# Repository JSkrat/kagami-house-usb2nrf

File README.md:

# Kagami house v3 — concentrator

usb to nrf24l01 radio network convertor

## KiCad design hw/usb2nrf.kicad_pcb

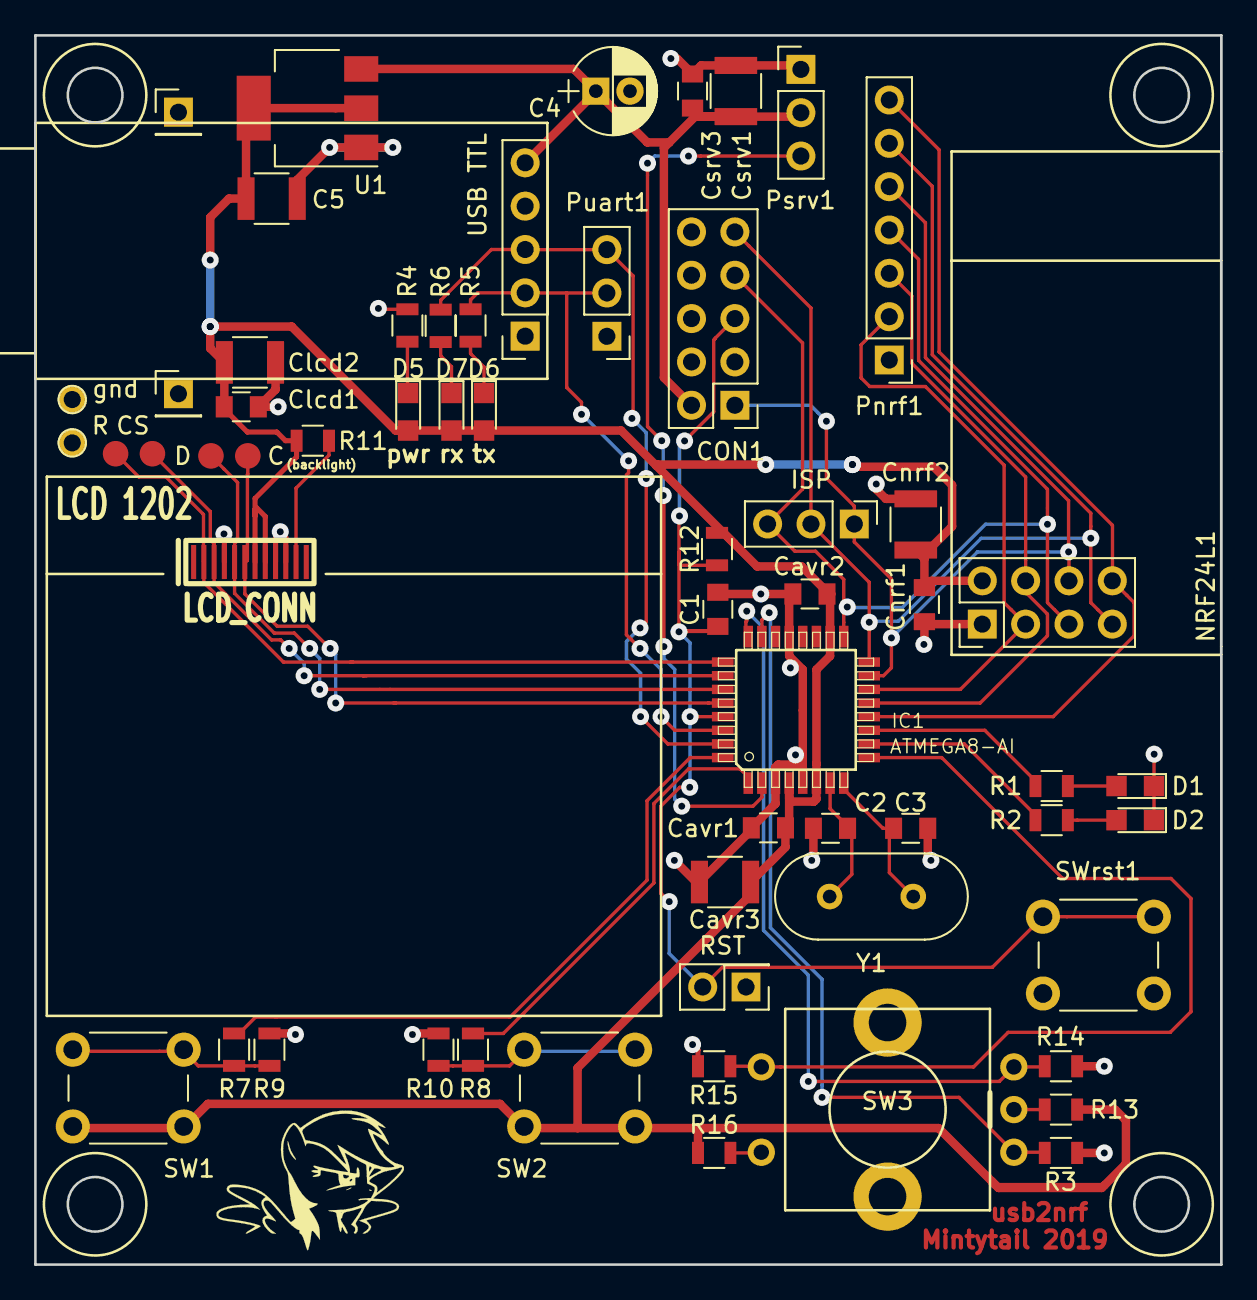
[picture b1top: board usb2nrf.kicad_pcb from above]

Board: 2 copper layers, 69.5 x 72.0 mm, 58 parts (0 on the bottom side), 36 nets.

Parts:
C: Measurement_Point_Round-SMD-Pad_Small
C1: 100n; C_0805
C2, C3: 22p; C_0805
C4: 10u; CP_Radial_D5.0mm_P2.00mm
C5: 10u; C_1210
CON1: AVR-JTAG-10; Pin_Header_Straight_2x05_Pitch2.54mm
CS: Measurement_Point_Round-SMD-Pad_Small
Cavr1, Cavr2: 100n; C_0805
Cavr3: 10u; C_1210
Clcd1: 100n; C_0805
Clcd2: 10u; C_1210
Cnrf1: 100n; C_0805
Cnrf2: 10u; C_1210
Csrv1: 10u; C_1210
Csrv3: 100n; C_0805
D: Measurement_Point_Round-SMD-Pad_Small
D1, D2, D5, D6, D7: LED; LED_0805
IC1: ATMEGA8-AI; atmega8-TQFP32-08
ISP: CONN_01X03; Pin_Header_Straight_1x03_Pitch2.54mm
LCD 1202: LCD_CONN; SIL-12
NRF24L1: NRF24L01; Pin_Header_Straight_2x04_Pitch2.54mm
P3, P6: CONN_01X01; Pin_Header_Straight_1x01_Pitch2.54mm
Pnrf1: nrf_test; Pin_Header_Straight_1x07_Pitch2.54mm
Psrv1: CONN_srv; Pin_Header_Straight_1x03_Pitch2.54mm
Puart1: uart_test; Pin_Header_Straight_1x03_Pitch2.54mm
R: Measurement_Point_Round-SMD-Pad_Small
R1, R2, R4, R5, R6, R11: R; R_0805
R3, R9, R10, R14, R15: 10k; R_0805
R7, R8: 150; R_0805
R12: 47k; R_0805
R13, R16: 511; R_0805
RST: CONN_01X02; Pin_Header_Straight_2x01_Pitch2.54mm
SW1, SW2: SW_Push; SW_PUSH_6mm_h4.3mm
SW3: Rotary_Encoder_Switch; encoder
SWrst1: SW_Push; SW_PUSH_6mm_h4.3mm
U1: AMS1117-3.3; SOT-223-3_TabPin2
USB TTL: USBTTL; Pin_Header_Straight_1x05_Pitch2.54mm
Y1: 16M; Crystal_HC18-U_Vertical
gnd: PINTST

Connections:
/3v3: C5.1, Cavr1.1, Cavr2.1, Cavr3.1, Clcd1.2, Clcd2.1, Cnrf1.2, Cnrf2.1, D5.2, D6.2, D7.2, IC1.4, IC1.6, IC1.18, LCD 1202.7, LCD 1202.8, NRF24L1.8, R11.2, R12.1, R13.1, R16.1, SW1.2, SW2.2, U1.2
/5v: C4.1, CON1.2, Csrv1.1, Csrv3.1, Psrv1.2, U1.3, USB TTL.5
/ce: IC1.14, NRF24L1.2, Pnrf1.2
/csn: IC1.13, NRF24L1.7, Pnrf1.3
/enc_btn: IC1.9, R15.1, SW3.S2
/irq: IC1.12, NRF24L1.5, Pnrf1.7
/lcd_backlight: LCD 1202.11, R11.1
/lcd_clk: C.1, IC1.28, LCD 1202.6
/lcd_cs: CS.1, IC1.26, LCD 1202.3
/lcd_rst: IC1.25, LCD 1202.2, R.1
/lcd_sda: D.1, IC1.27, LCD 1202.5
/miso: CON1.9, IC1.16, ISP.2, NRF24L1.4, Pnrf1.6
/mosi: CON1.1, IC1.15, ISP.1, NRF24L1.6, Pnrf1.5
/reset: C1.1, CON1.5, IC1.29, R12.2, RST.2, SWrst1.1
/rx_usb: IC1.31, Puart1.3, R6.1, USB TTL.3
/sck: CON1.7, IC1.17, ISP.3, NRF24L1.3, Pnrf1.4
/tx_usb: IC1.30, Puart1.2, R5.1, USB TTL.2
/xtal1: C2.1, IC1.7, Y1.1
/xtal2: C3.1, IC1.8, Y1.2
GNDPWR: C1.2, C2.2, C3.2, C4.2, C5.2, CON1.4, CON1.6, CON1.8, CON1.10, Cavr1.2, Cavr2.2, Cavr3.2, Clcd1.1, Clcd2.2, Cnrf1.1, Cnrf2.2, Csrv1.2, Csrv3.2, D1.1, D2.1, IC1.3, IC1.5, IC1.21, LCD 1202.4, LCD 1202.9, LCD 1202.10, NRF24L1.1, P3.1, P6.1, Pnrf1.1, Psrv1.1, Puart1.1, R3.2, R4.2, R9.2, R10.1, R14.2, R15.2, RST.1, SW3.6, SWrst1.2, U1.1, USB TTL.4, gnd.1
unnamed: D1.2, R1.2
unnamed: D2.2, R2.2
unnamed: D5.1, R4.1
unnamed: D6.1, R5.2
unnamed: D7.1, R6.2
unnamed: IC1.1, R8.2
unnamed: IC1.2, Psrv1.3
unnamed: IC1.10, R2.1
unnamed: IC1.11, R1.1
unnamed: IC1.23, R3.1, SW3.A
unnamed: IC1.24, R14.1, SW3.B
unnamed: IC1.32, R7.2
unnamed: R7.1, R9.1, SW1.1
unnamed: R8.1, R10.2, SW2.1
unnamed: R13.2, SW3.C
unnamed: R16.2, SW3.S1

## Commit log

2019-01-17 initial commit: presumable scheme, firmware with n1202 screen and "egg" of command parser
2019-01-17 make it compilable
2019-01-22 fixed uart patch int2str functions to l-string instead of z-string
2019-01-23 parser: last command, stub response for status command lcdRamPrint fix
2019-01-26 include nrf24l01 library receive loop uart packet parser rework transmission is not done yet
2019-01-28 adapt 1202_lib to -mint8 flag switch to 200kbit because of pl2303 better debug on screen now nrf works! switch CE off before the transmission start appears to be an important thing usart protocol upd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
2019-02-10 unworking update: from addresses to pipes
2019-11-07 adjust lcd direction update defines to new test board update parsers to new documentation ui subsystem needs debugging
2019-12-01 add software to get all modem status
2019-12-01 debug sw: improve console, add payload to transmitting packets
2019-12-01 hw: update kicad version
2019-12-01 sw: normal, byte-by-byte serial parser, fixed signatures of terminal messages
2019-12-15 add "ok, listening" response to valid responses
2019-12-31 sw: optimizations, add command to switch modem mode
2019-12-31 hgignore
2019-12-31 fw: merge with other copy, add set mode and set master address commands add pullup for miso
2019-12-31 fw: add rf packet parser structure
2019-12-31 fw: generated messagesc and messages.h to gitignore
2020-01-01 fw: validating request and generate error response
2020-01-01 fw: response data for transaction id error
2020-01-07 fw: add rf functions except write channel
2020-01-12 attempt to create tests for functions and rf parser part using boost
2020-01-19 fw: add unit tests (gtest, cmake) for functions.c: ListOfUnits, SetMacAddress, GetRFStatistics, GetPropertiesOfUnit fw: fix bugs in tested functions
2020-02-23 architecture: separate unit structure to a separate file tests: finish read channel tests bugfix: read channel is working now
2020-02-24 functions: add write channels function tests: adjust for WO channels, improvements
2020-02-24 hgignore update
2020-03-03 fw: refactoring, split protocol from rf interface add read mode along with set mode (uart) unit tests are broken now(((
2020-03-03 sw: implement serial queue to avoid command glitches
2020-03-03 fw: add forgotten protocol files
2020-03-05 fw tests: split them to files, optimize segment initiaalization, now it is being restored before every test (and has magic) also optimize dependencies a little in the fw itself
2020-03-07 fw refactoring: make functions inputs const add "reset transaction id" function use structure of the packet instead of offsets enum fw tests: update to change test new function add testing protocol t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
2020-03-07 fw: add function NOP, remove control and validation of transaction id bugfix protocol multiplexor add dummy system unit 0 fw tests: better initialization of function tests fixed get list of units tes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
2020-03-09 fw protocol: fix unit_structure inclusion, update validation for tests, remove double response too big code fw rf: refactor rf events callbacks fw tests: add string map for return codes for better me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
2020-03-11 fw: add response timeout, make master behaviour, untested yet
2020-03-11 sw debugger: fix serial timeout, increase it to 50ms
2020-03-16 fw: add forgotten two last registers to 00 uart request (1C dynpd and 1D feature)
2020-03-16 sw debugger: rename buttons remove queued message if unable to send
2020-03-28 sw: start new transaction immediately after finishing one
2020-03-28 sw: centralize serial transaction timeout
2020-03-28 sw: show serial queue size in the statusbar
2020-03-28 sw: fix serial queue
2020-03-29 sw: fix fifo tx_full checkbox
2020-04-12 fw: optimize 1202 lib to avoid unused fonts
2020-04-12 fw: refactoring RF parser to avoid it knowing about uart - isolate low-level wrapper so RF model now utilizes callbacks, not ISR, thus, it knows nothing about initialization and nrf workflow (except 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
2020-04-19 fw refactoring: UART functions
2020-04-19 fw refactoring: add suffix to RF protocol and functions files
2020-04-20 fw: uart response generator function fix rest includes after last refactoring
2020-04-20 fw: complete moving packet parsing functional to UART protocol.c remove extra includes
2020-04-20 fw: adapt to unit tests fw unit tests: adapt to refactored code
2020-04-20 fw unit tests: create test suite for uart functions testing
2020-04-26 fw: optimization for unit testing bugfixes of uart protocol parser change command numbers for status and addresses add command echo (not implemented)
    fw tests: more function dummies
    uart functions testing framework
    uart protocol testing
2020-04-26 fw: uart function readRFBuffer
2020-04-26 sw: remove obsolete function codes, update codes to new version
2020-04-26 fw tests: remove obsolete checks and catches
2020-04-27 sw: update to new protocol, obtain packets from buffer manually
2020-04-27 fw: remove old protocol code from uart parser (wrong version)
2020-05-03 fw tests: attempt to create RF model test
2020-05-03 fw tests: forgotten files(((
2020-05-03 fw tests: make them great again =)
2020-05-03 fw: refactor nrf24 library calls entirely out of RF model bugfix ListenAddress in transmitting as master
2020-05-03 fw tests: update for latest refactoring add tests for buffer, callbacks fw: add check for null in allocating new item from rf buffer add counter missed_packets instead of unused transaction_errors bu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
2020-05-09 fw: wrap lcd module into ifdef
2020-05-09 fw protocol: move response code from the payload to a personal field
2020-05-09 fw: bugfix uart sender
2020-05-09 sw: update debugger to updated protocol
2020-05-09 sw: attempt to fix segfault at dequeue
2020-05-09 fw: flush tx buffer after ack timeout
2020-05-09 sw: proper initialization of serial parser
2020-05-09 sw: nicify messages, make them correct mark rx and tx of uart
2020-05-10 fw: add build number to the uart functions
2020-05-10 sw: show build number in the window title
2020-05-11 sw: build number in hex
2020-05-11 fw: control CE, optimize register reading bugfix rf response length sw: test response length for wrong packets
2020-05-11 fw bugfix: do not call irq callback on irq reset
2020-05-11 fw: duplex transmission achieved
2020-05-11 fw bugfix: initialize payload length for ack and timeout packets
2020-05-11 sw bugfix: transmission power level interpretation
2020-05-11 fw: increase timeout and retransmission attempts
2020-05-11 fw: disable auto acknowledgement implement rf statistics update tests
2020-05-11 fw: comments
2020-05-11 fw: documentation
2020-05-13 fw: add set rf channel rf function
2020-05-13 fw: adjust tests for new function exists
2020-05-13 fw: remove "next rf channel" field from rf request header
2020-05-16 add gitignore
2020-05-16 fw: split master and slave modes into two separate firmwares add settings module
2020-05-16 better gitignore
2020-05-17 fw: advertisement, implement function switch rf channel, switch slave mode, optimize switching rf channel (do not switch to the same)
2020-05-17 fw: bugfix advertisement. Adv and additional functions are ok
2020-05-17 fw: save rf channel on change bugfix packet receiving
2020-05-17 fw: switch rf functions vector to map
2020-05-17 fw refactoring: move units structure structures to its header
2020-05-23 documentation
2020-05-23 fw: functions refactoring. Standart functions for all units and separate lists of individual functions make separate file for custom unit functions (all not protocol related)
2020-05-23 fw: update protocol.c to new RF functions structure add "function" argument to all rf functions
2020-05-23 fw: prototype complete! additional structure to map function number to port/pin to reuse same functions for multiple pins implement get/set pin
2020-05-23 fw: add switch to use timer2 instead of timer0 for slave advertisement
2020-05-23 fw: remove unused ui module, remove unused mode switch function (we have defines for that now)
2020-05-23 fw: add servo control for fun
2020-05-23 fw: probably fixed rf function get unit properties
2020-05-23 fw: add get/set unit description functions really fix get unit properties function
2021-03-27 add packet constructor add packet decoder
2021-06-26 attempt to create framework black debug actuator alpha
2021-06-26 update gitignore
